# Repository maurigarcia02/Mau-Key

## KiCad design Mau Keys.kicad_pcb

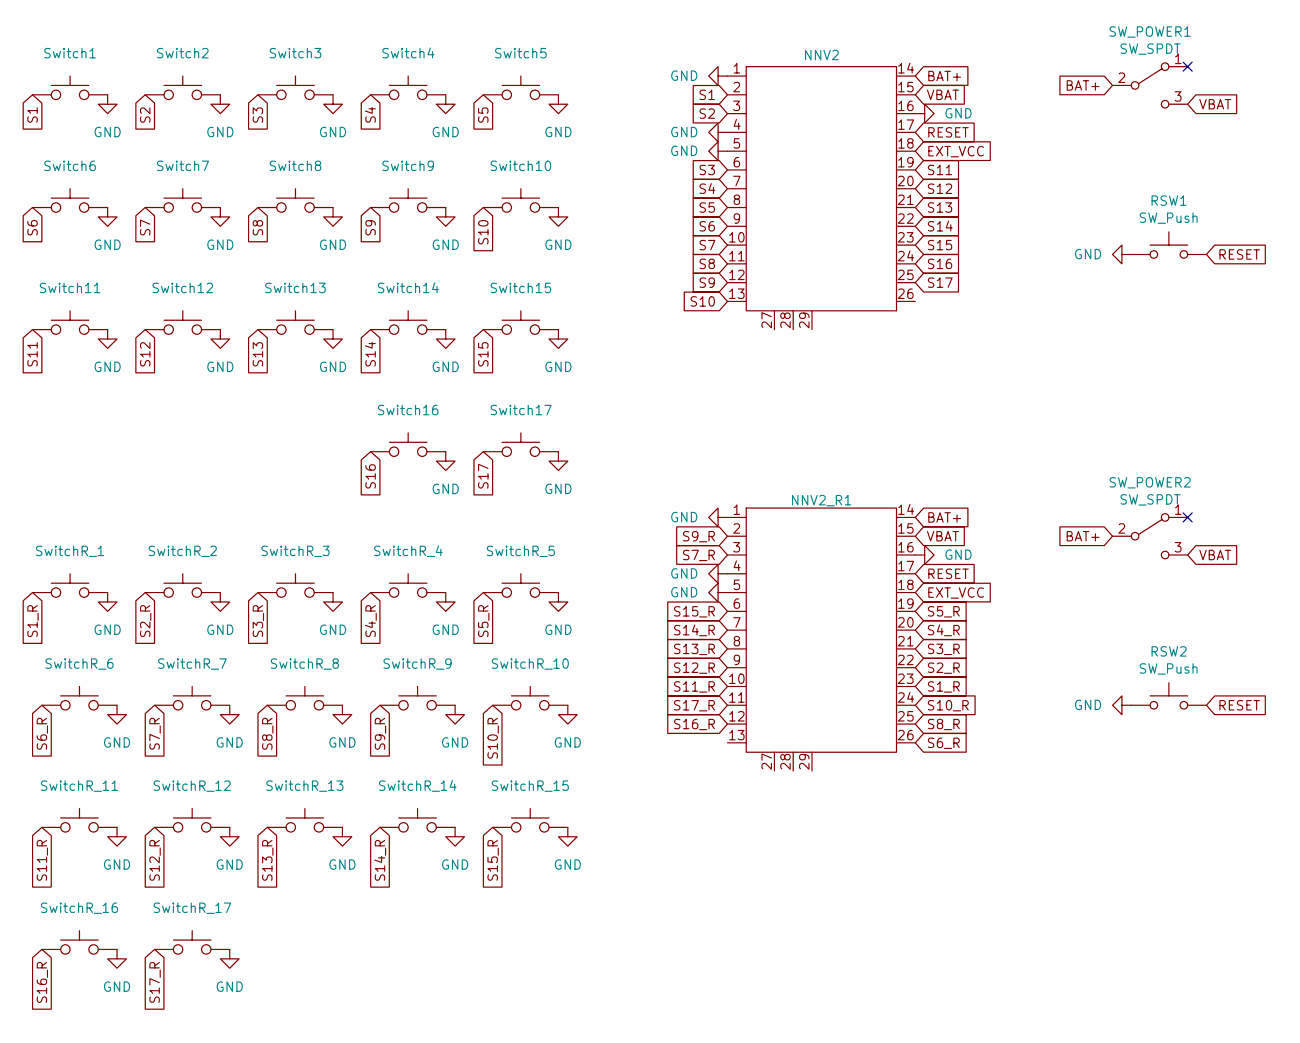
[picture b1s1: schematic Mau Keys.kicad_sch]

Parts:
NNV2, NNV2_R1: nice_nano
RSW1, RSW2: SW_Push; SW_RESET
SW_POWER1, SW_POWER2: SW_SPDT; smt-slider-switch
Switch1, Switch2, Switch3, Switch4, Switch5, Switch6, Switch7, Switch8, Switch9, Switch10, Switch11, Switch12, Switch13, Switch14, Switch15, Switch16, Switch17: keyswitch_cherrymx_alps_choc12_slots_1u
SwitchR_1, SwitchR_2, SwitchR_3, SwitchR_4, SwitchR_5, SwitchR_6, SwitchR_7, SwitchR_8, SwitchR_9, SwitchR_10, SwitchR_11, SwitchR_12, SwitchR_13, SwitchR_14, SwitchR_15, SwitchR_16, SwitchR_17: keyswitch_cherrymx_alps_choc12_slots_1u

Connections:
BAT+: NNV2.14, NNV2_R1.14, SW_POWER1.2 (B), SW_POWER2.2 (B)
EXT_VCC: NNV2.18, NNV2_R1.18
GND: NNV2.1, NNV2.4, NNV2.5, NNV2.16, NNV2_R1.1, NNV2_R1.4, NNV2_R1.5, NNV2_R1.16, RSW1.1, RSW2.1, Switch1.2, Switch2.2, Switch3.2, Switch4.2, Switch5.2, Switch6.2, Switch7.2, Switch8.2, Switch9.2, Switch10.2, Switch11.2, Switch12.2, Switch13.2, Switch14.2, Switch15.2, Switch16.2, Switch17.2, SwitchR_1.2, SwitchR_2.2, SwitchR_3.2, SwitchR_4.2, SwitchR_5.2, SwitchR_6.2, SwitchR_7.2, SwitchR_8.2, SwitchR_9.2, SwitchR_10.2, SwitchR_11.2, SwitchR_12.2, SwitchR_13.2, SwitchR_14.2, SwitchR_15.2, SwitchR_16.2, SwitchR_17.2
RESET: NNV2.17, NNV2_R1.17, RSW1.2, RSW2.2
S1: NNV2.2, Switch1.1
S1_R: NNV2_R1.23, SwitchR_1.1
S2: NNV2.3, Switch2.1
S2_R: NNV2_R1.22, SwitchR_2.1
S3: NNV2.6, Switch3.1
S3_R: NNV2_R1.21, SwitchR_3.1
S4: NNV2.7, Switch4.1
S4_R: NNV2_R1.20, SwitchR_4.1
S5: NNV2.8, Switch5.1
S5_R: NNV2_R1.19, SwitchR_5.1
S6: NNV2.9, Switch6.1
S6_R: NNV2_R1.26, SwitchR_6.1
S7: NNV2.10, Switch7.1
S7_R: NNV2_R1.3, SwitchR_7.1
S8: NNV2.11, Switch8.1
S8_R: NNV2_R1.25, SwitchR_8.1
S9: NNV2.12, Switch9.1
S9_R: NNV2_R1.2, SwitchR_9.1
S10: NNV2.13, Switch10.1
S10_R: NNV2_R1.24, SwitchR_10.1
S11: NNV2.19, Switch11.1
S11_R: NNV2_R1.10, SwitchR_11.1
S12: NNV2.20, Switch12.1
S12_R: NNV2_R1.9, SwitchR_12.1
S13: NNV2.21, Switch13.1
S13_R: NNV2_R1.8, SwitchR_13.1
S14: NNV2.22, Switch14.1
S14_R: NNV2_R1.7, SwitchR_14.1
S15: NNV2.23, Switch15.1
S15_R: NNV2_R1.6, SwitchR_15.1
S16: NNV2.24, Switch16.1
S16_R: NNV2_R1.12, SwitchR_16.1
S17: NNV2.25, Switch17.1
S17_R: NNV2_R1.11, SwitchR_17.1
VBAT: NNV2.15, NNV2_R1.15, SW_POWER1.3 (C), SW_POWER2.3 (C)

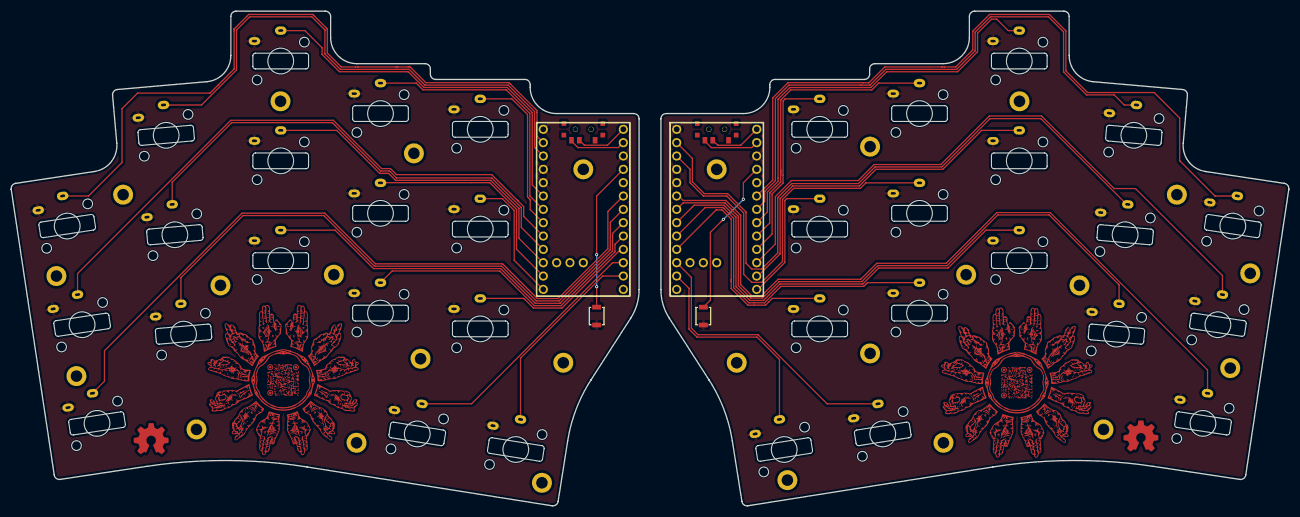
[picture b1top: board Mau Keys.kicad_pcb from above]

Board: 2 copper layers, 243.3 x 94.2 mm, 40 parts (0 on the bottom side), 39 nets.

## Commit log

2025-03-27 Commit inicial, Add switch fp
2025-03-29 holaaa
2025-04-04 Initial traces
2025-04-05 nada
2025-04-06 hola2
2025-04-09 Add traces upper left
2025-04-16 Traces upper left
2025-04-26 dxf de teclado
2025-04-27 traces lado izquierdo
2025-05-11 finished left
2025-05-11 detallitos
2025-05-26 fix switch fp
2025-05-26 fix switch traces
2025-10-13 Nueva geometria
2025-10-26 new arrangement
2025-11-03 pcb casi terminado
2025-11-04 pcb final
